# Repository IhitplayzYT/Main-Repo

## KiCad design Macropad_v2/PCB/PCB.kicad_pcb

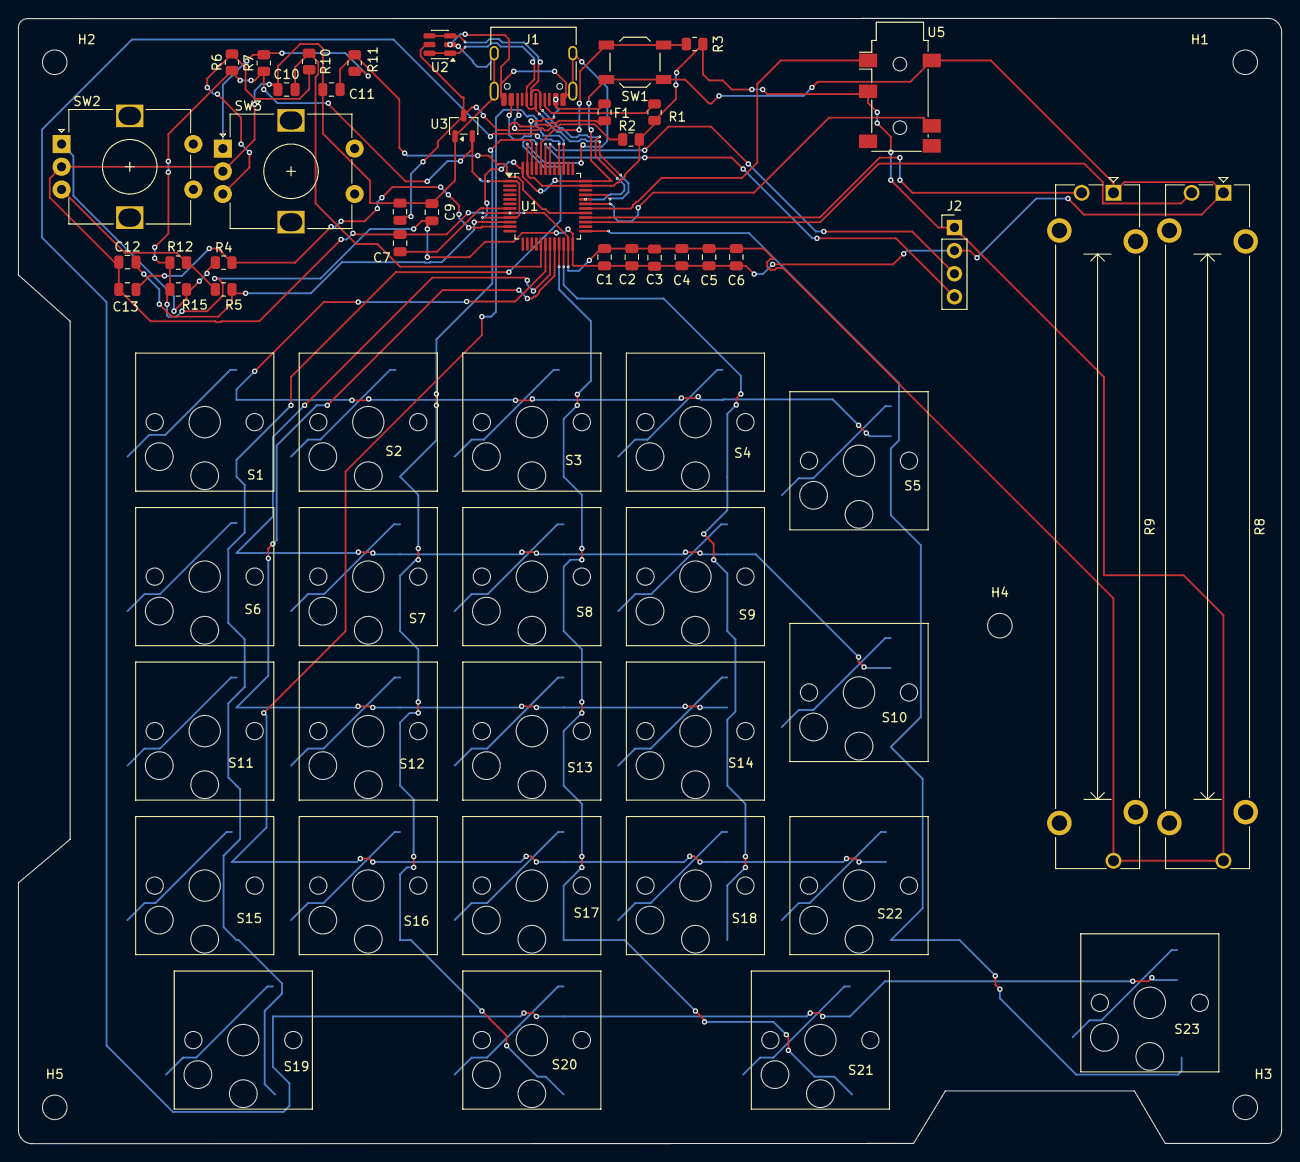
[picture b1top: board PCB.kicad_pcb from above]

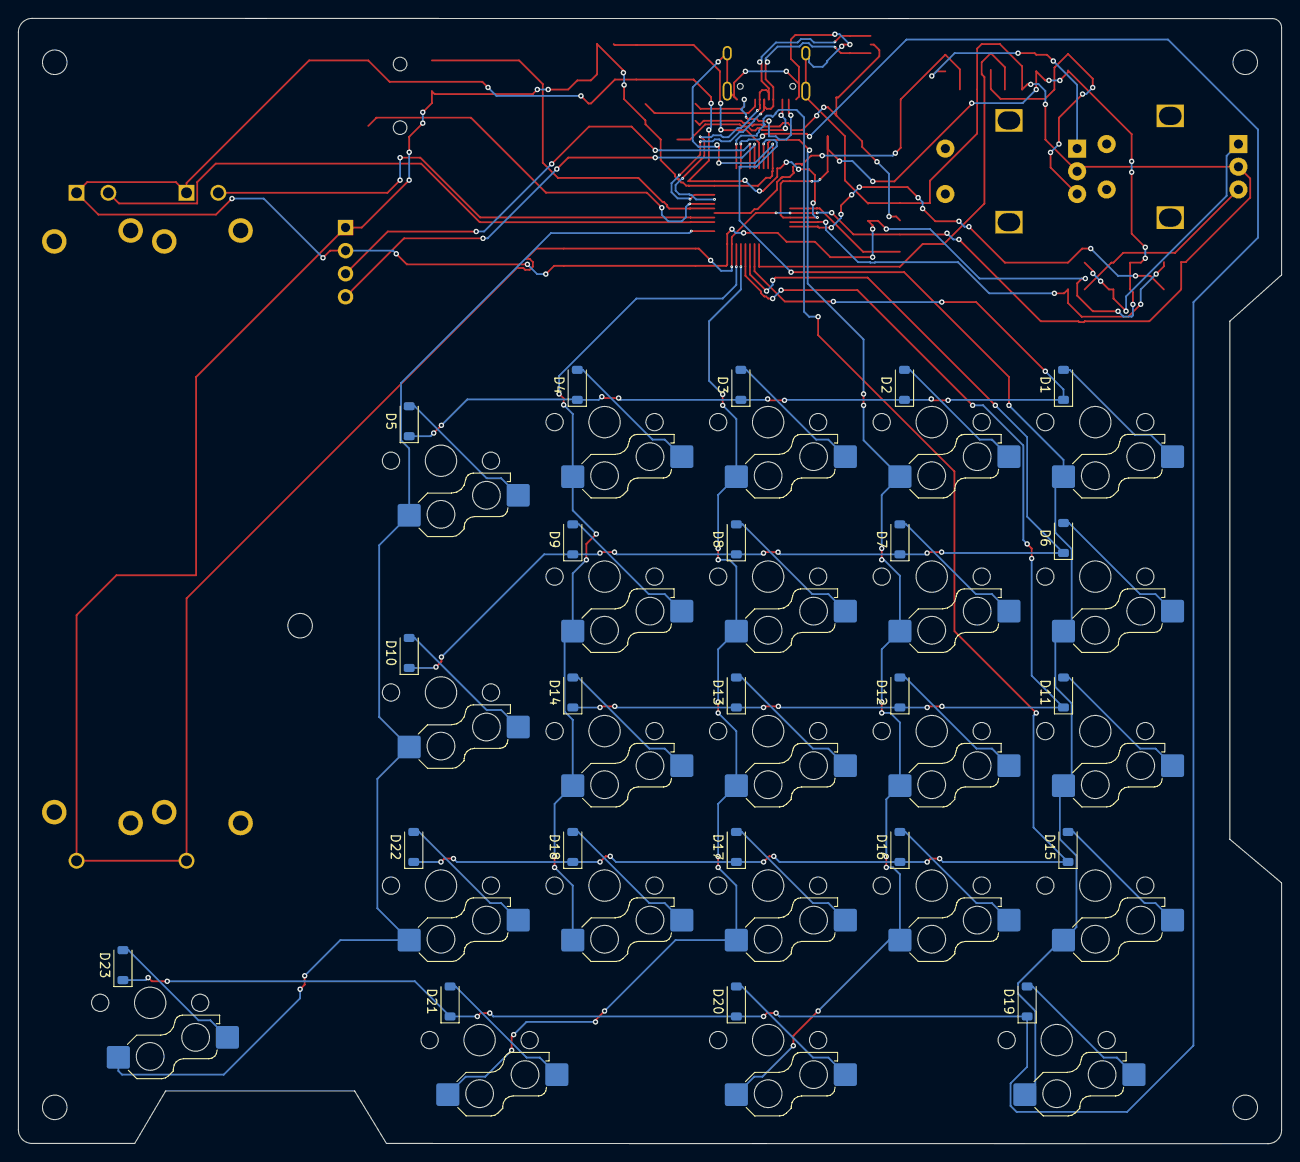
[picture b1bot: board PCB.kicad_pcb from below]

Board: 2 copper layers, 139.0 x 123.8 mm, 87 parts (23 on the bottom side), 57 nets.

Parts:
C1, C2, C3, C4, C5, C7: 100nF; C_0805_2012Metric
C6, C10, C11, C12, C13: 10nF; C_0805_2012Metric
C8, C9: 1uF; C_0805_2012Metric
D1, D2, D3, D4, D5, D6, D7, D8, D9, D10, D11, D12, D13, D14, D15, D16, D17, D18, D19, D20, D21, D22, D23: D_SOD-123
F1: 500mA; Fuse_0805_2012Metric
H1, H2, H3, H4, H5: MountingHole; MountingHole_2.7mm
J1: USB_C_Receptacle_USB2.0_14P; USB_C_Receptacle_HRO_TYPE-C-31-M-12
J2: OLED_128x64; PinHeader_1x04_P2.54mm_Vertical
R1, R2: 5.1k; R_0805_2012Metric
R3, R4, R5, R6, R7, R10, R11, R12, R15: 10k; R_0805_2012Metric
R8, R9: Potentiometer; Potentiometer_Bourns_PTA6043_Single_Slide
S1, S2, S3, S4, S5, S6, S7, S8, S9, S10, S11, S12, S13, S14, S15, S16, S17, S18, S19, S20, S21, S22, S23: Hotswap_Choc_V1_1.00u
SW1: SW_Push; SW_SPST_TL3342
SW2, SW3: RotaryEncoder; RotaryEncoder_Alps_EC12E-Switch_Vertical_H20mm
U1: STM32F072CBTx; LQFP-48_7x7mm_P0.5mm
U2: USBLC6-2SC6; SOT-23-6
U3: XC6206; SOT-23-3
U5: TRRS; Jack_3.5mm_PJ311_Horizontal

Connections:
+3.3V: C1.1, C2.1, C3.1, C4.1, C5.1, C6.1, C9.1, J2.2 (VCC), R6.1, R7.1, R8.1, R9.1, R12.1, R15.1, SW1.1, U1.1 (VBAT), U1.9 (VDDA), U1.24 (VDD), U1.36 (VDDIO2), U1.48 (VDD), U3.2 (VO), U5.2 (TIP)
+5V: C8.1, F1.2, U2.5 (VBUS), U3.3 (VI)
BOOT: R3.1, SW1.2, U1.44 (BOOT0)
C0: S1.1, S6.1, S11.1, S15.1, S19.1, U1.45 (PB8)
C1: S2.1, S7.1, S12.1, S16.1, S20.1, U1.46 (PB9)
C2: S3.1, S8.1, S13.1, S17.1, S21.1, U1.21 (PB10)
C3: S4.1, S9.1, S14.1, S18.1, U1.22 (PB11)
C4: S5.1, S10.1, S22.1, S23.1, U1.25 (PB12)
D+: J1.A6 (D+), J1.B6 (D+), U1.33 (PA12), U2.1 (I/O1), U2.6 (I/O1)
D-: J1.A7 (D-), J1.B7 (D-), U1.32 (PA11), U2.3 (I/O2), U2.4 (I/O2)
GND: C1.2, C2.2, C3.2, C4.2, C5.2, C6.2, C7.1, C8.2, C9.2, C10.1, C11.1, C12.1, C13.1, J1.A1 (GND), J1.A12 (GND), J1.B1 (GND), J1.B12 (GND), J1.SH (SHIELD), J2.1 (GND), R1.2, R2.2, R3.2, R8.3, R9.3, SW2.C, SW3.C, U1.8 (VSSA), U1.23 (VSS), U1.35 (VSS), U1.47 (VSS), U2.2 (GND), U3.1 (GND), U5.3 (RING1)
unnamed: D1.2 (A), S1.2
unnamed: D2.2 (A), S2.2
unnamed: D3.2 (A), S3.2
unnamed: D4.2 (A), S4.2
unnamed: D5.2 (A), S5.2
unnamed: D6.2 (A), S6.2
unnamed: D7.2 (A), S7.2
unnamed: D8.2 (A), S8.2
unnamed: D9.2 (A), S9.2
unnamed: D10.2 (A), S10.2
unnamed: D11.2 (A), S11.2
unnamed: D12.2 (A), S12.2
unnamed: D13.2 (A), S13.2
unnamed: D14.2 (A), S14.2
unnamed: D15.2 (A), S15.2
unnamed: D16.2 (A), S16.2
unnamed: D17.2 (A), S17.2
unnamed: D18.2 (A), S18.2
unnamed: D19.2 (A), S19.2
unnamed: D20.2 (A), S20.2
unnamed: D21.2 (A), S21.2
unnamed: D22.2 (A), S22.2
unnamed: D23.2 (A), S23.2
unnamed: J1.A5 (CC1), R1.1
unnamed: J1.B5 (CC2), R2.1
unnamed: R6.2, R10.1, SW3.B
unnamed: R7.2, R11.1, SW3.A
unnamed: R5.1, R12.2, SW2.B
unnamed: R4.1, R15.2, SW2.A
unnamed: C7.2, U1.7 (NRST)
R0: D1.1 (K), D2.1 (K), D3.1 (K), D4.1 (K), D5.1 (K), U1.18 (PB0)
R1: D6.1 (K), D7.1 (K), D8.1 (K), D9.1 (K), D10.1 (K), U1.19 (PB1)
R2: D11.1 (K), D12.1 (K), D13.1 (K), D14.1 (K), U1.20 (PB2)
R3: D15.1 (K), D16.1 (K), D17.1 (K), D18.1 (K), D22.1 (K), U1.39 (PB3)
R4: D19.1 (K), D20.1 (K), D21.1 (K), D23.1 (K), U1.40 (PB4)
RE_1_A: C12.2, R5.2, U1.10 (PA0)
RE_1_B: C13.2, R4.2, U1.11 (PA1)
RE_2_A: C10.2, R10.2, U1.17 (PA7)
RE_2_B: C11.2, R11.2, U1.29 (PA8)
RX: U1.31 (PA10), U5.4 (RING2)
SCL: J2.3 (SCL), U1.42 (PB6)
SDA: J2.4 (SDA), U1.43 (PB7)
SLIDER_1: R8.2, U1.27 (PB14)
SLIDER_2: R9.2, U1.28 (PB15)
TX: U1.30 (PA9), U5.1 (SLEEVE)
VBUS: F1.1, J1.A4 (VBUS), J1.A9 (VBUS), J1.B4 (VBUS), J1.B9 (VBUS)

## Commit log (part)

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2025-06-05 Initial build-system for C as of right now
2025-06-05 Added the toraliser project that routes Ipv4 addresses of websites through a tor proxy[WITHOUT DNS resolver]
2025-06-10 Added simple HTML live server rip[oinly serves /app/webpage requests as of now]
2025-07-11 c headers added
2025-07-22 Added File modifier project
2025-07-22 Fixed Server working with html css and js....not complete integration with apis a tags etc
2025-07-24 Added Stack library
2025-07-27 Added a queue implementation
2025-07-27 Updated the C_Header folder
2025-08-17 Ihit Utils with some QOL fxns for c
2025-08-18 Hashmap implementation added
2025-08-20 Fixed hashmap.h
2025-08-20 Added Binary Search tree
2025-09-09 Modified the BuildSystemCTemplate (Added private/public functionalities alongside the Malloc macros)
2025-09-20 Upcoming super project backup
2025-09-20 New Massive project
2025-09-20 Fixed & added functionality to hash_set
2025-09-27 Major progress of Filesystem with working filesystem and fsformat and bitmasking fxn done with valid writes to drives from disk emulator
2025-09-27 Added MRM TP work i have done
2025-09-29 Added fsmount/unmount and inode funcctionality
2025-09-30 Started on GUI using C & Assembly
2025-10-03 Basic gui development on Bios framebuffer(40x25) complete alongside working on shifting to vga mode buffer with started work in creation of bmp files and bmp file parser
2025-10-04 Finished embedder( Takes in a input and outputs a hexadecimal file compatible to c and assembly files)
2025-10-06 Adding of a printf function, Added read and write to DOS files alongside majority of bmp parser and printer function
2025-10-07 Added snprintf,printf,and fixing the parse_bmp(status is BM signature successgit add .git add .F)
2025-10-09 started work on the inodes functions of the filesystem
2025-10-11 Fixed and added functionalitites to inodes alongside helper fxns for filesystem
2025-10-13 A mini project of a sql database that has been normalised to BCNF alongside fxns,procedures and triggers for a college administration database in oracle sqlplus
2025-10-14 Started Networking project to integrate with OS_DEV project
2025-10-15 Massive Haul to stdoslib with _Generics and ongoing work with generics strict ===
2025-10-16 Finished full backend of Networks now being able to send raw Ip packets and reciever raw packets alongside parsing of the packets....Minor bugs and USAGE and cleanup left to do
2025-10-17 Massive updates to stdoslib.h now added full support to python like min,max and sort fxn with both scalar and vector support for min max fxns
2025-10-17 Added print array fxn
2025-10-18 Working on implementing OOP and vector in c
2025-10-18 Added more vector progress
2025-10-19 Finished vector implem with Iterator object support
2025-10-20 Added the new keyword noe being able to use a syntax similar to java for object creation
2025-10-21 Added Filter functionality
2025-10-22 Javascript and html learning as of right now, NO CSS,Supersimpledev practice on javascript
2025-10-23 Networks.c cleanup and successful working
2025-10-23 Finished and added many improvemnts to the Network module now allowing me to send recieve ICMP echo packets while integrating timeout for unresponsive IPs alongside making it CLI environmental usage
2025-10-24 Added in work hyperland config + Started work on Time capabilities to stdoslib.h
2025-10-24 added some of my rice configs
2025-10-24 Added some more of my rice configs
2025-10-25 Started work on Ethernet Layer packet parsing
2025-10-26 Finished work on tuples for multiple value returns and also finsihed most of the work for global deallocator in stdoslib
2025-10-28 Added ticks and date time support to stdoslib.h
2025-10-29 Added some thernet functionalities liek show and init along side with healp[er fxns to networks.h
2025-10-30 Added some more functionality to string operations in stdoslib.h
2025-11-01 Added hex to ascii and vice versa functions to stdoslib.h alongide started work on a directory path simplification function for fs.c
2025-11-01 Notes updated
2025-11-02 Added tokeniser functionality to stdoslib.h
2025-11-03 Added major updates and fixes to stdoslib.h along with completeion of pathname evaluator
2025-11-04 Added mutlple helper fxns to stdoslib.h started work on validating and formatting filenames alongside troubleshooting, Going to start directory integration
2025-11-05 Major progress in fs.c with now capabilites to search directories alongside path parsing for directory nesting
2025-11-06 Debugging day of the fs.h
2025-11-08 Some util functionality and bug troubleshooting
2025-11-10 Not much progress just some prototypes and ideas for future
2025-11-11 Updated some notes
2025-11-15 Some work on a FIND/fzf based utility in fs.h
2025-11-15 Added some sample Mini DBS made
2025-11-16 Starting a very interesting project for dynamic runtime loading of C code: PRIMARY USECASE: GUI.h to finetune params for perfects bitmap output
2025-11-22 small changes nothing much another week before active new projectsa nd development
2025-12-11 Finished hotreloader project to dynamically load code during runtime
2025-12-15 Started Work on my projected LONGEST Production Ready compiler for a custom language of my own[Current progress : Lexing finished with proper tokenisation]
2025-12-18 Debugging in OS_DEV project
2025-12-20 Learning ML
2025-12-20 Added GUI project that renders 64kiB bitmap images to a VGA msdos output
2025-12-21 KNN done from scratch
2025-12-22 Studied assembly and some microarchitecture of CPU
2025-12-27 95 % progress on the C code hotreloading via dyuynamically linked libarraies
2026-01-03 Chnages to buildsys C_template,MOdifications to HotReload and starting of new Project a C_preprocessor to add native C++ like features in C
2026-01-05 Trying to make a production ready Black scholes option prizer[Using Rust-C-Python FFI with rust and c for mathematic computations and visualisations in python]<Future plans for async and multithreade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
2026-01-08 Added BM_25 indexer
2026-01-08 FINALLY fixed the fatall segfault and made some small changes to fxns
2026-01-10 Removed some warnign and errors and also removed cycling partial dependencies between files
2026-01-10 Work on the snowball porter
2026-01-15 Updates to many files?
2026-01-15 Added the Goscrapper project
2026-01-16 Finished adding all the string searcher functions and tydied up main
2026-01-17 Added major progress to BM25 indexer
2026-01-19 Updated Compiler and GOscrapper
2026-01-19 Added my MRM github
2026-01-19 Added compiler and major changes
2026-01-20 Added DNS resolver and mostly done with parser aside from shorthands
2026-01-20 Added my new project DNS resolver alongside also adding the updated Compiler project
2026-01-21 Finished DNS Resolver project
2026-01-22 Fixing some bugs in OS project added some documentation to OS
2026-01-23 Finished adding documentation to OS_DEV, Major progress on BM25 indexer
2026-01-23 Mkdir function add but segfaults
2026-01-27 Added the print trait for the parser in Compiler project
2026-01-27 Added updated PreRustC with defer and @Autowired completed
2026-01-27 Added some helper and major skeleton for Goscrapper
2026-01-27 Added some skelteon and helper functions to goscraper
2026-01-28 Added updated PreRustC
2026-01-29 Debugged all features are now working! Only step remaining is to convert a token stream back to fromated text , The preprocess supports Null Coalesing ??= , ?. Optional access chains , defer macro fo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
2026-02-04 Started and almost finished the Bootloader project to be used in OSDEV
2026-02-05 Added Updated projects for bootloader goscrapper and prerustc
2026-02-06 UPdated PreRustC with proper .h file parsing and population of structs
2026-02-06 UPdated polished refined and completed my oldest and my first project with easy installation & deletion via makefile and tidied up readme , added more templates to use
2026-02-06 Updated Preprocessor mostly done just fixing up defer and deferc left alongisde the creation file and temp files functionality
2026-02-06 Updated Goscrapper with job pool and Godownloader updated to work with base64 raw html encoded images
2026-02-06 Updated BM25 indexer
2026-02-07 Finished the BM25 based Search Engine with Stopword removal,Two types of stemmer support of SNowball and Lanchaster, Reactive TUI for real time sorting and updating of results of the best file matches
2026-02-07 Almost 99 % done except the defer macro is breaking i found a fix but s=there is a bug but for now just the reconcat fxns are remaining
2026-02-08 Updated almost finsished Goscrapper added rate limiting and timer with support for levenshtein based word thresholding
2026-02-10 Finally finished with almost all logic of PreRustC had to drop cpp init as it interfered with some native c fxn call syntax
2026-02-11 Usage and finally fix some issues with printing now fully working as intended features
2026-02-12 Updated PreRustC now with for each loop to iterate byte by byte
2026-02-12 Updated Networks project with documentation
2026-02-13 Added updated Goscrapper now able to uncompress files
2026-02-14 Restarted the Network project finished with some ethernet functionalities
2026-02-15 Added documentation
2026-02-16 Documentation Added
2026-02-16 Finished Rust part of Black scholes
2026-02-16 Fixed some bugs/issues in the Networks code
2026-02-17 Added mutli assign to prerustc, added updated version of OS_DEV
2026-02-17 Started work on robots.txt compliance in Goscrapper
2026-02-17 Added more features to PreRustC with python style multiassign and for each looops for string
2026-02-17 Added makefile and README to Stdoslib project
2026-02-17 Goscrapper updated with robots.txt comliance
2026-02-19 UPdated Compiler after a long while
2026-02-21 Added springboot project
2026-02-21 Updated Readme of PreRustC
2026-02-22 Frontend docs added
2026-02-22 Finished Compiler frontend
2026-02-23 Added documentation to Compiler
2026-02-24 Added intepretor repo
2026-02-24 Fixed intepretor github
2026-02-25 Added documentation to Interpretor
2026-02-27 Updated stdoslib
2026-02-28 Almost finished documentation of the majority of Interpretor
2026-02-28 Added updated verison of stdoslib
2026-03-01 Added some missing expression evaluation functions and almost finished all the documentation for Interpretor
2026-03-02 Updated both compiler and interpretor with full documentation, fixes and support for new tokens like **,++,--,<<=,>>=
2026-03-06 Workign on adding struct and enums to the compiler/interpretor and maybe bytecode machine
2026-03-07 Updated the interpretor
2026-03-09 Some changes made to Interpretor
2026-03-12 added linux drivers repo
2026-03-13 Added mutable paramaters to the functions
2026-03-14 Updated Interpretor code with bug fixes now fully set for IR and code gen
2026-03-16 Added parameter parsing to the interpretor
2026-03-18 Updated zecrovixsr still on kvm trying to implement multiple vcpu and smp support
2026-03-19 Added Dbus and mmio and pio functions interface structs and better errors to the ZecroVizR
2026-03-19 Some more progress including finsihing some of the mutlithreaded and smp cpu fd spawning feature
2026-03-20 Added documentation tpo the ZecroVizR
2026-03-29 Updated codes
2026-03-31 FINALLY done with the Interprtor project there are still some tiniy bugs or unexpected outputs however bulk is finished except for enum integration in codegen
2026-03-31 Updated Vlux-_KDD
2026-04-01 Modularising and integrating the APIs... now only implementation of CLI is left
2026-04-02 Finished the Interpretor projectaand also started the new project Torquent,with the progress consisting of implementing and finishing the boilerplate and also almsot finished writing the ben parser f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
2026-04-13 Added new project repo RelNeCraph
2026-04-17 Updated WITH ROUTING FINSIHED for macropad
2026-04-17 Added new repo Ifrit and updated macropad
2026-05-03 Updated macropad
2026-05-18 Added Vigifile and also updated buildsys
2026-05-19 Updated Vigifile
2026-06-07 Added up to date CStaM and SpeRu Projects
2026-06-07 Updated CStaM
2026-06-08 Updated Speru and CStaM
2026-06-13 Added finished CStam and highly updated Speru
2026-06-13 Added echo mini img
2026-06-16 Added PixCu++
2026-06-23 Added updated versions of PieZo EzpeR and LangCompose
2026-06-26 Updated EzpeR
2026-06-27 Finished LangCompose
